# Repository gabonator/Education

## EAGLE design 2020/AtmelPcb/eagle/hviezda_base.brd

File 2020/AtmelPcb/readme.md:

# Electro workshop 4 - Standalone doska

Minimalne zapojenie bateriou napajaneho mikrokontrolera atmel ATTiny84 s diodami a spinacom v tvare Vianocnej hviezdice. Jas diod je riadeny softarovou implementaciou modifikovaneho PWM algoritmu. Mikrokontroler programujeme s pomocou ICSP interfacu, na tento ucel mozeme pouzit vhodny programator alebo lubovolne ine arduino. Pozrieme sa na moznosti, ako predlzit zivotnost bateriou napajaneho zariadenia a ake komponenty vyzaduje mikrokontroler pre svoju prevadzku.

## Video

## Anotacia

Blížia sa Vianoce a Creative Point má pre Vás výnimočnú príležitosť vyrobiť si programovateľnú vianočnú ozdobu, v ktorej bude bežať Váš vlastný program. Navrhneme dosku plošného spoja s mikrokontrolérom ATTiny84, piatimi LED diódami a spínačom v programe Eagle. Celé zariadenie bude plniť funkciu blikajúcej dekoračnej ozdoby na vianočný stromček v tvare päťcípej hviezdy.

Dosku plošného spoja vyrobíme na CNC fréze metódou isolation milling, osadíme súčiastkami a zletujeme. Vysvetlíme si, ako prebieha programovanie prostredníctvom interfacu ICSP a ako použiť Arduino IDE priamo na programovanie mikrokontrolérov Atmel. Pozrieme sa na to, aké sú možnosti zníženia spotreby mikrokontroléra, aby nám batériou napájané zariadenie vydržalo čo najdlhšie.

Vysúšame si zopár jednoduchých animácií s reguláciou jasu LED diódy a na záver si vytvoríte vlastný program, kde tieto animácie skombinujete do výsledného programu v jazyku C, ktorý bude bežať vo Vašom výrobku.

Na workshop potrebujete:
Laptop a USB Mini kábel
Arduino IDE: https://www.arduino.cc/en/software
Autodesk Eagle: https://www.autodesk.com/products/eagle/free-download

## Beseda

Ak sa spomenie pojem Arduino, väčšina z vás si predstaví zelenú doštičku osadenú mikrokontrolérom Atmel s konektormi na pripojenie periférií a USB konektorom na programovanie. Kód, ktorý napíšeme v jazyku C sa po jednom kliknutí v prostredí Arduino IDE skompiluje do inštrukcií a napáli do procesora, ktorý ho bude potom vykonávať. 

Arduino je však prototypovacia platforma, ktorá slúži na jednoduché a rýchle otestovanie zapojenia. Ak by sme náš návrh chceli povýšiť do podoby finálneho zariadenia, je vhodne navrhnúť vlastnú dosku plošného spoja (DPS) s minimálnymi rozmermi a minimálnym počtom komponentov, aby sme znížili výrobné náklady. 

Dosku vyrobíme s využitím technológií, ktoré máme v Creative Pointe k dispozícii. Namiesto obľúbenej technológie výroby plošných spojov “foto cestou” ju vyrobíme na CNC fréze technikou “isolation milling”, kedy z medenej fólie na kuprextite odstránime časti, ktoré nepotrebujeme a ponecháme iba tie, ktoré budú viesť elektricky prúd. Výhodou takéhoto prístupu je rýchla výroba prototypu bez využitia chemikálií.

Ak aj takúto dosku vyrobíme a osadíme súčiastkami, zariadenie ešte nebude fungovať. Je potrebné vykonať ešte jeden dôležitý krok - nahrať firmware do mikrokontroléra. Pri platforme Arduino je to jednoduché - väčšina Arduino dosiek je vybavená konektorom USB na pripojenie počítača. Medzi mikrokontrolérom a USB konektorom je však ďalší komponent, tzv. USB transceiver, ktorý prevádza prijaté USB packety do signálov, ktorým mikrokontrolér rozumie. Ale aj to ho vopred musíme “naučiť”. Po zapnutí mikrokontroléra sa na niekoľko sekúnd aktivuje program, tzv. bootloader, ktorý čaká na signály z počítača a v prípade potreby je pripravený preprogramovať svoju pamäť. Ak sa nič nedeje, bootloader spustí program, ktorý sme tam predtým napálili.

Ak však vyrábame jednoduché jednoúčelové zariadenie, ktoré nebude potrebné preprogramovať, je zbytočné na neho montovať takýto port a ďalšie podporné elektronické komponenty. Každý programovateľný procesor je možné nejakým spôsobom preprogramovať, a každý z výrobcov používa buď vlastný interface a protokol, alebo sa v praxi zaužíval tzv. JTAG interface, ktorý popri programovaní poskytuje možnosť aj odlaďovať (debugovať) bežiaci program.

8 bitové procesory Atmel využívajú vlastný protokol nazvaný ICSP, tento sa na doskách Arduino nachádza v podobe 2x3 pinovej hlavičky. Tá okrem troch komunikačných signálov (clock, data in, data out) obsahuje resetovací signál, zem a napájanie.

V našom projekte využijeme 14 pinový čip ATTiny84, namiesto čipu ATMega328p, ktorý sa nachádza na doskách Arduino Uno R3, alebo Arduino Mini. V závislosti od zložitosti projektu volíme čo najmenší procesor, ktorý nám s dostatočnou rezervou vystačí z hľadiska výkonu (frekvencia procesora), kapacity Flash pamäte (pamäť inštrukcií programu), RAM pamäte (pamäť na premenné), a taktiež z hľadiska dostupných periférií a spotreby elektrickej energie. ATTiny84 sme zvolili z dôvodu nižšieho počtu pinov a celkovo menšieho rozmeru. Pripájať naňho budeme iba 5 LED diód a jeden prepínač. Zároveň potrebujeme 4 piny na programovací interface ICSP. 

Nevýhoda využitia procesora ATTiny84 je tá, že nedisponuje generátorom PWM na každom pine. Pre nás to znamená, že ak chceme regulovať jas LED diódy, budeme si musieť naprogramovať softwarovú implementáciu PWM, ktorá bude systematicky rozblikávať diódu vo vhodných intervaloch.

Po oživení a otestovaní zariadenia toto odpojíme od programovacieho interfacu ICSP a overíme jeho spotrebu na 3V batérii typu CR2032. Vyskúšame metódy na zníženie spotreby - keďže táto je závislá od taktu procesora a aktivovaných periférií, vysvetlíme si ako povypínať tieto periférie, ako použiť interný oscilátor prítomný priamo v mikropočítači a taktiež využijeme prechod do úsporného režimu “sleep”. Po vyčíslení spotreby počas behu programu a počas spánku skúsime odhadnúť výdrž zariadenia pri pripojení na jednu CR2032 batériu.

## BOM

- Nakup pre 8 ucastnikov kurzu dokopy 51.99 eur

| Pocet | Co                            | Oznacenie GME/TME                             | Jednotkova cena | Celkova cena | Linka         |
|-------|-------------------------------|-----------------------------------------------|-----------------|--------------|---------------|
| 8x    | AtTiny84, DIP14               | ATTINY84-20PU MICROCHIP (ATMEL)               | 2.6             | 20.8         | https://www.tme.eu/sk/details/attiny84-20pu/modelovy-rad-avr-8-bit/microchip-atmel/ |
| 8x    | Mikrospinac                   | Mikrospínač TC-0103-T (WM)                    | 0.11            | 0.88         | https://www.gme.sk/tc-0103-t |
| 40x   | Rezistor 470Ohm               | Metalizovaný rezistor RM 470R 0207 0,6W 1%    | 0.11            | 4.4          | https://www.gme.sk/rm-470r-0207-0-6w-1 | 
| 40x   | Cervena LED 5mm obycajna      | LED 5MM RED 400/50                            | 0.09            | 3.6          | https://www.gme.sk/led-5mm-red-400-50-bl-bje5v4v-2 |
| 1x    | Lista rovna 2x40              | Kolíková lišta S2G80 2,54mm                   | 0.39            | 0.39         | https://www.gme.sk/oboustranny-kolik-s2g80-2-54mm |
| 8x    | Kondenzator 100n              | Keramický kondenzátor CK 100n/100V X7R RM5,08 | 0.11            | 0.88         | https://www.gme.sk/ck-100n-100v-x7r-rm5-08-10-hitano |
| 8x    | Drziak baterie CR2032         | Držáik baterie do DPS DS1092-04 B6P           | 0.22            | 1.76         | https://www.gme.sk/drzaik-baterie-do-dps-ds1092-04-b6p |
| 8x    | Bateria CR2032                | Westinghouse CR2032 3V 220mAh lithiová        | 0.71            | 5.68         | https://www.gme.sk/baterie-gombikova-westinghouse-cr2032-3v-220mah-lithiova |
| 5x    | Doska PCB 20x10cm             | Cuprextit 200x100x1,5mm, jednovrstvový EPCU200X100 | 2.72       | 13.6         | https://www.gme.sk/cuprextit-200x100x1-5-jednovrstvy |

- Na programovanie a testovanie potrebujeme 8x Arduino Uno (alebo ine) a 6+1 pinovy M-F kabel pre kazdeho (8x7=56 kablov)
- 1 kabel M-F na testovanie led diod

## Materialy

- [Material](material.md)
- [Prezentacia](prezentacia.pdf)

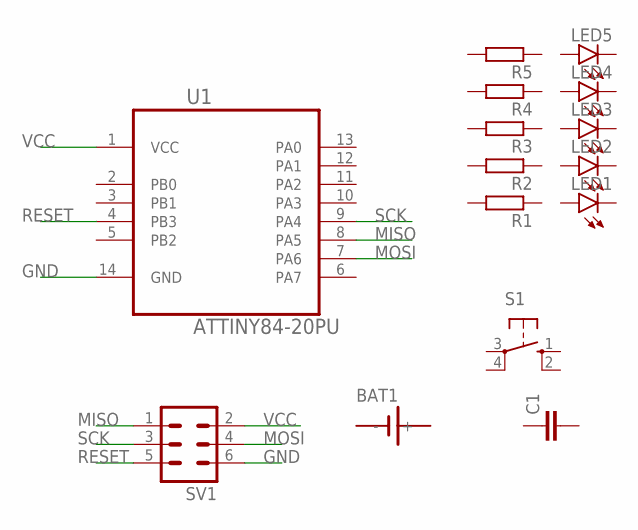
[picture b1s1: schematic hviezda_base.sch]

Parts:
BAT1: SN2032
C1: C-EU050-024X044; C050-024X044
LED1, LED2, LED3, LED4, LED5: LED5MM
R1, R2, R3, R4, R5: R-EU_0207/10; 0207/10
S1: 10-XX; B3F-10XX
SV1: MA03-2
U1: ATTINY84-20PU; DIP254P762X533-14

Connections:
GND: SV1.6, U1.14 (GND)
MISO: SV1.1, U1.8 (PA5)
MOSI: SV1.4, U1.7 (PA6)
RESET: SV1.5, U1.4 (PB3)
SCK: SV1.3, U1.9 (PA4)
VCC: SV1.2, U1.1 (VCC)

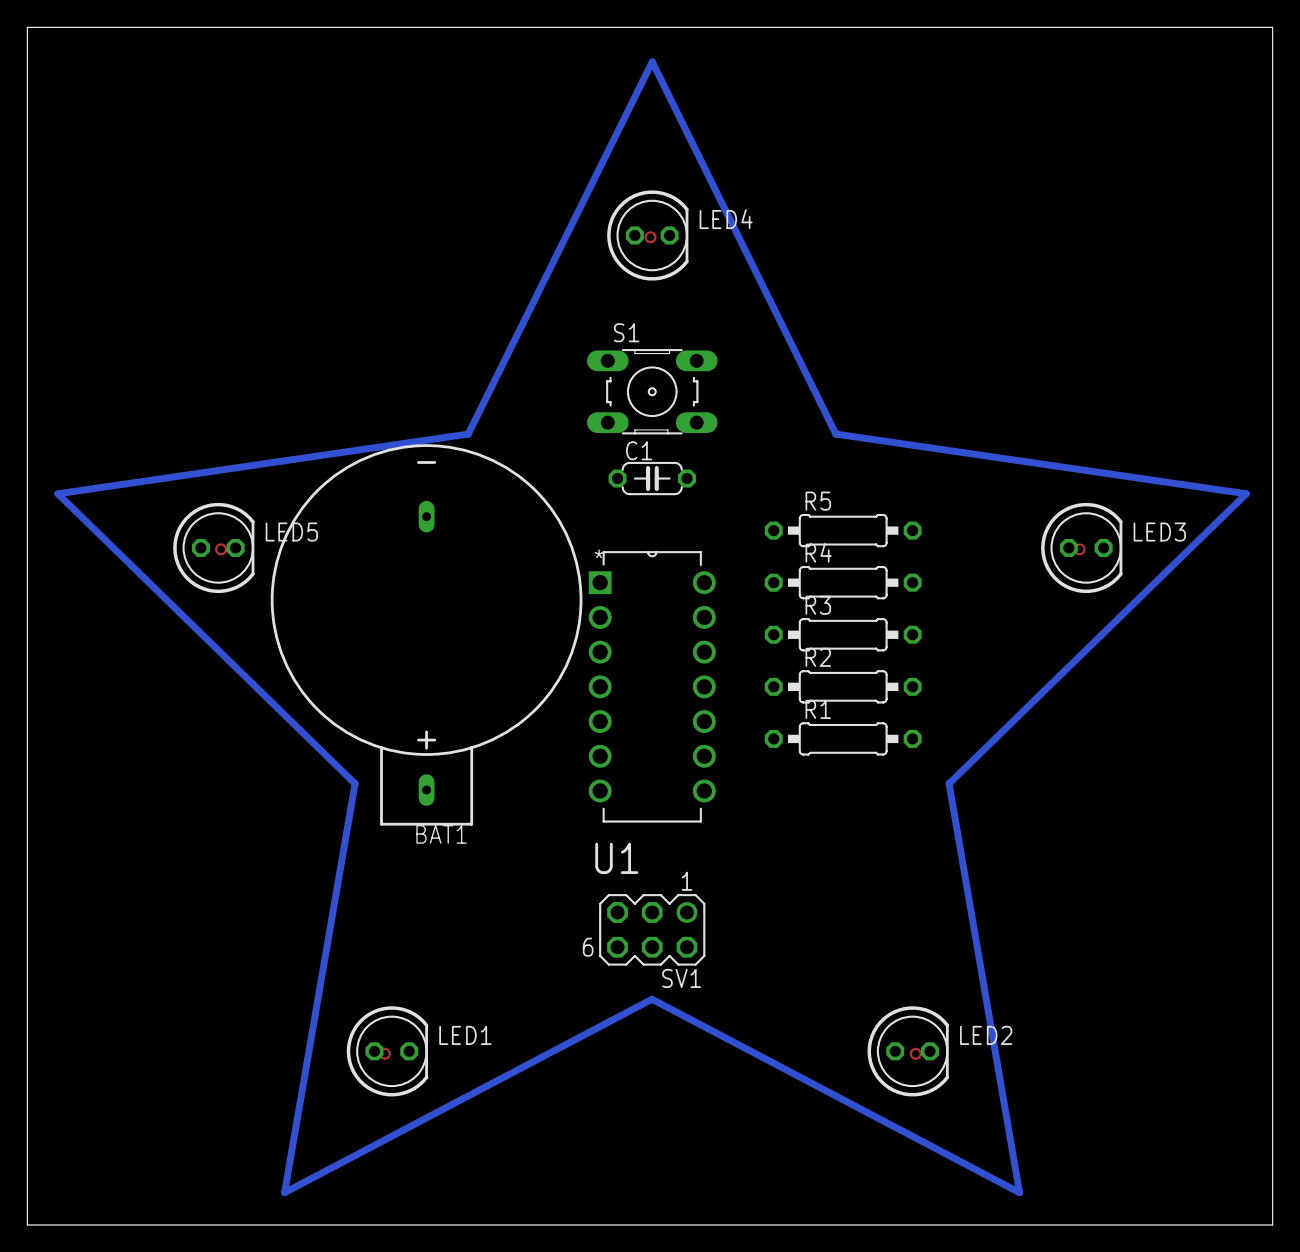
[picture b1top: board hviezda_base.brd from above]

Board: 2 copper layers, 91.1 x 87.6 mm, 15 parts (0 on the bottom side), 6 nets.

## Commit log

2019-12-23 intial commit
2019-12-24 webusb update
2019-12-24 education projects moved here from Work-In-Progress repository
2019-12-24 wrong picture
2019-12-24 image resize test
2019-12-24 working resized images
2020-03-07 electro 1 workshop
2020-03-08 workshop 2 raw BOM
2020-03-08 bom tables
2020-03-08 led symbol terminals
2020-03-15 useless box update, added camera pan tilt stand model
2020-04-05 projects summary
2020-04-05 stupid word
2020-04-07 rift zapper reverse engineering
2020-04-07 formatting
2020-04-13 updated video url
2020-07-12 Electro 2 workshop
2020-07-12 workshop 2 update
2020-08-15 workshop useless box
2020-08-15 electro workshop 3
2020-11-08 standalone atmel board workshop with ATTINY84
2020-11-26 blikajuca hviezda update
2020-12-12 AtmelPcb workshop update
2020-12-13 nove programy
2020-12-26 cicoparser readme
2020-12-26 typos
2021-01-03 moved to 2021
2021-01-03 logo update, added video
2021-01-03 logo size
2021-01-03 resize
2021-01-03 aaaah
2021-01-10 added screenshots
2021-04-15 readme update
2021-04-15 wrong path
2021-04-16 space
2021-04-19 cv update
2021-04-21 programming1
2021-04-25 new games added
2021-04-27 fix table
2021-04-28 workshop update
2021-04-28 resized
2021-04-28 resize image
2021-04-29 update added canvas code
2021-04-29 tasks in separate markup file
2021-05-02 finalize
2021-05-02 link to onlinegdb
2021-06-08 intial commit - electro workshop 4 - esp8266 with oled display
2021-06-09 converted to 128x64 oled
2021-06-10 new photo
2021-06-19 workshop preparation guide
2021-06-27 typo
2021-06-28 oled library animation
2021-07-07 interactive demos
2021-07-28 workshop update, added programs and screenshots
2021-08-04 all exercises prepared
2021-08-07 arduino nano alternative
2021-08-07 smaller collision image
2021-08-08 support for arduino uno
2021-08-09 sun drawing
2021-08-15 advanced tasks
2021-08-15 renamed electro4 to electro5
2021-08-15 some stuff
2021-08-15 updated links to new folder
2021-08-16 updated presentations, added one task
2021-08-18 some extra programs for loops and functions
2021-10-23 alta gate reverse engineering
2021-10-23 decoded example
2021-10-25 main script recovered from AF.exe
2021-11-01 electro workshop 2
2021-11-01 updated bom calculation
2021-11-21 annotation
2022-01-10 web1 workshop
2022-03-06 electro workshop: led decoration with attiny45
2022-03-06 photos
2022-03-07 print settings
2022-03-13 moved to 2022
2022-03-16 final
2022-04-21 frozen bubble game
2022-04-24 workshop steps
2022-05-02 updated task list
2022-05-04 readme
2022-05-04 chrome preview
2022-05-07 more tasks ready
2022-05-08 samsung smart tv app
2022-05-08 missing image
2022-05-12 updated list of tasks, empty template package, homework
2022-05-14 diff update
2022-05-14 diff links
2022-05-15 unified diff
2022-07-15 electro 7 workshop
2022-07-23 typo fix
2022-08-09 presentation for first session
2022-08-13 cleanup
2022-08-14 rename
2022-09-22 intro for second workshop
2023-02-21 treti programovaci workshop - sokoban v javascripte
2023-03-05 presentation
2023-03-14 url update
2023-05-04 mini update
2023-05-10 update, fixing typos
2023-12-29 2023 update
2024-02-10 Christmas tree stand
